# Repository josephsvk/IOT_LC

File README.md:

# IOT_LC

KiCad hardware project for the modular IoT controller.

## Project files

- `IOT_LC.kicad_pro` — KiCad project settings
- `IOT_LC.kicad_sch` — schematic
- `IOT_LC.kicad_pcb` — PCB layout
- `IOT_LC.kicad_dru` — custom design rules
- `IOT_LC.csv` — component list

**Status:** Work in progress; not validated for production.

**Safety:** The design includes mains voltage. It has not been certified or validated for safe mains operation. Do not assume it is safe to manufacture or energize.

## Automatic PCB render

The user systemd path watcher monitors `IOT_LC.kicad_pcb`. After the file has
been unchanged for 2.5 seconds, it regenerates the top and bottom 3D renders.
The watcher unit files are in `systemd/`; the manual command is
`./rychle-spustenie/render.sh`.

<!-- AUTO-DOCS-START -->
## Schematic documentation

### Complete active hierarchical schematic

**Page 1**

[View vector PDF](docs/pdf/schematic.pdf)

## PCB documentation

### PCB front

**Page 1**

[View vector PDF](docs/pdf/pcb-front.pdf)

### PCB back

**Page 1**

[View vector PDF](docs/pdf/pcb-back.pdf)

### 3D render — pohľad zhora

### 3D render — pohľad zdola

<!-- AUTO-DOCS-END -->

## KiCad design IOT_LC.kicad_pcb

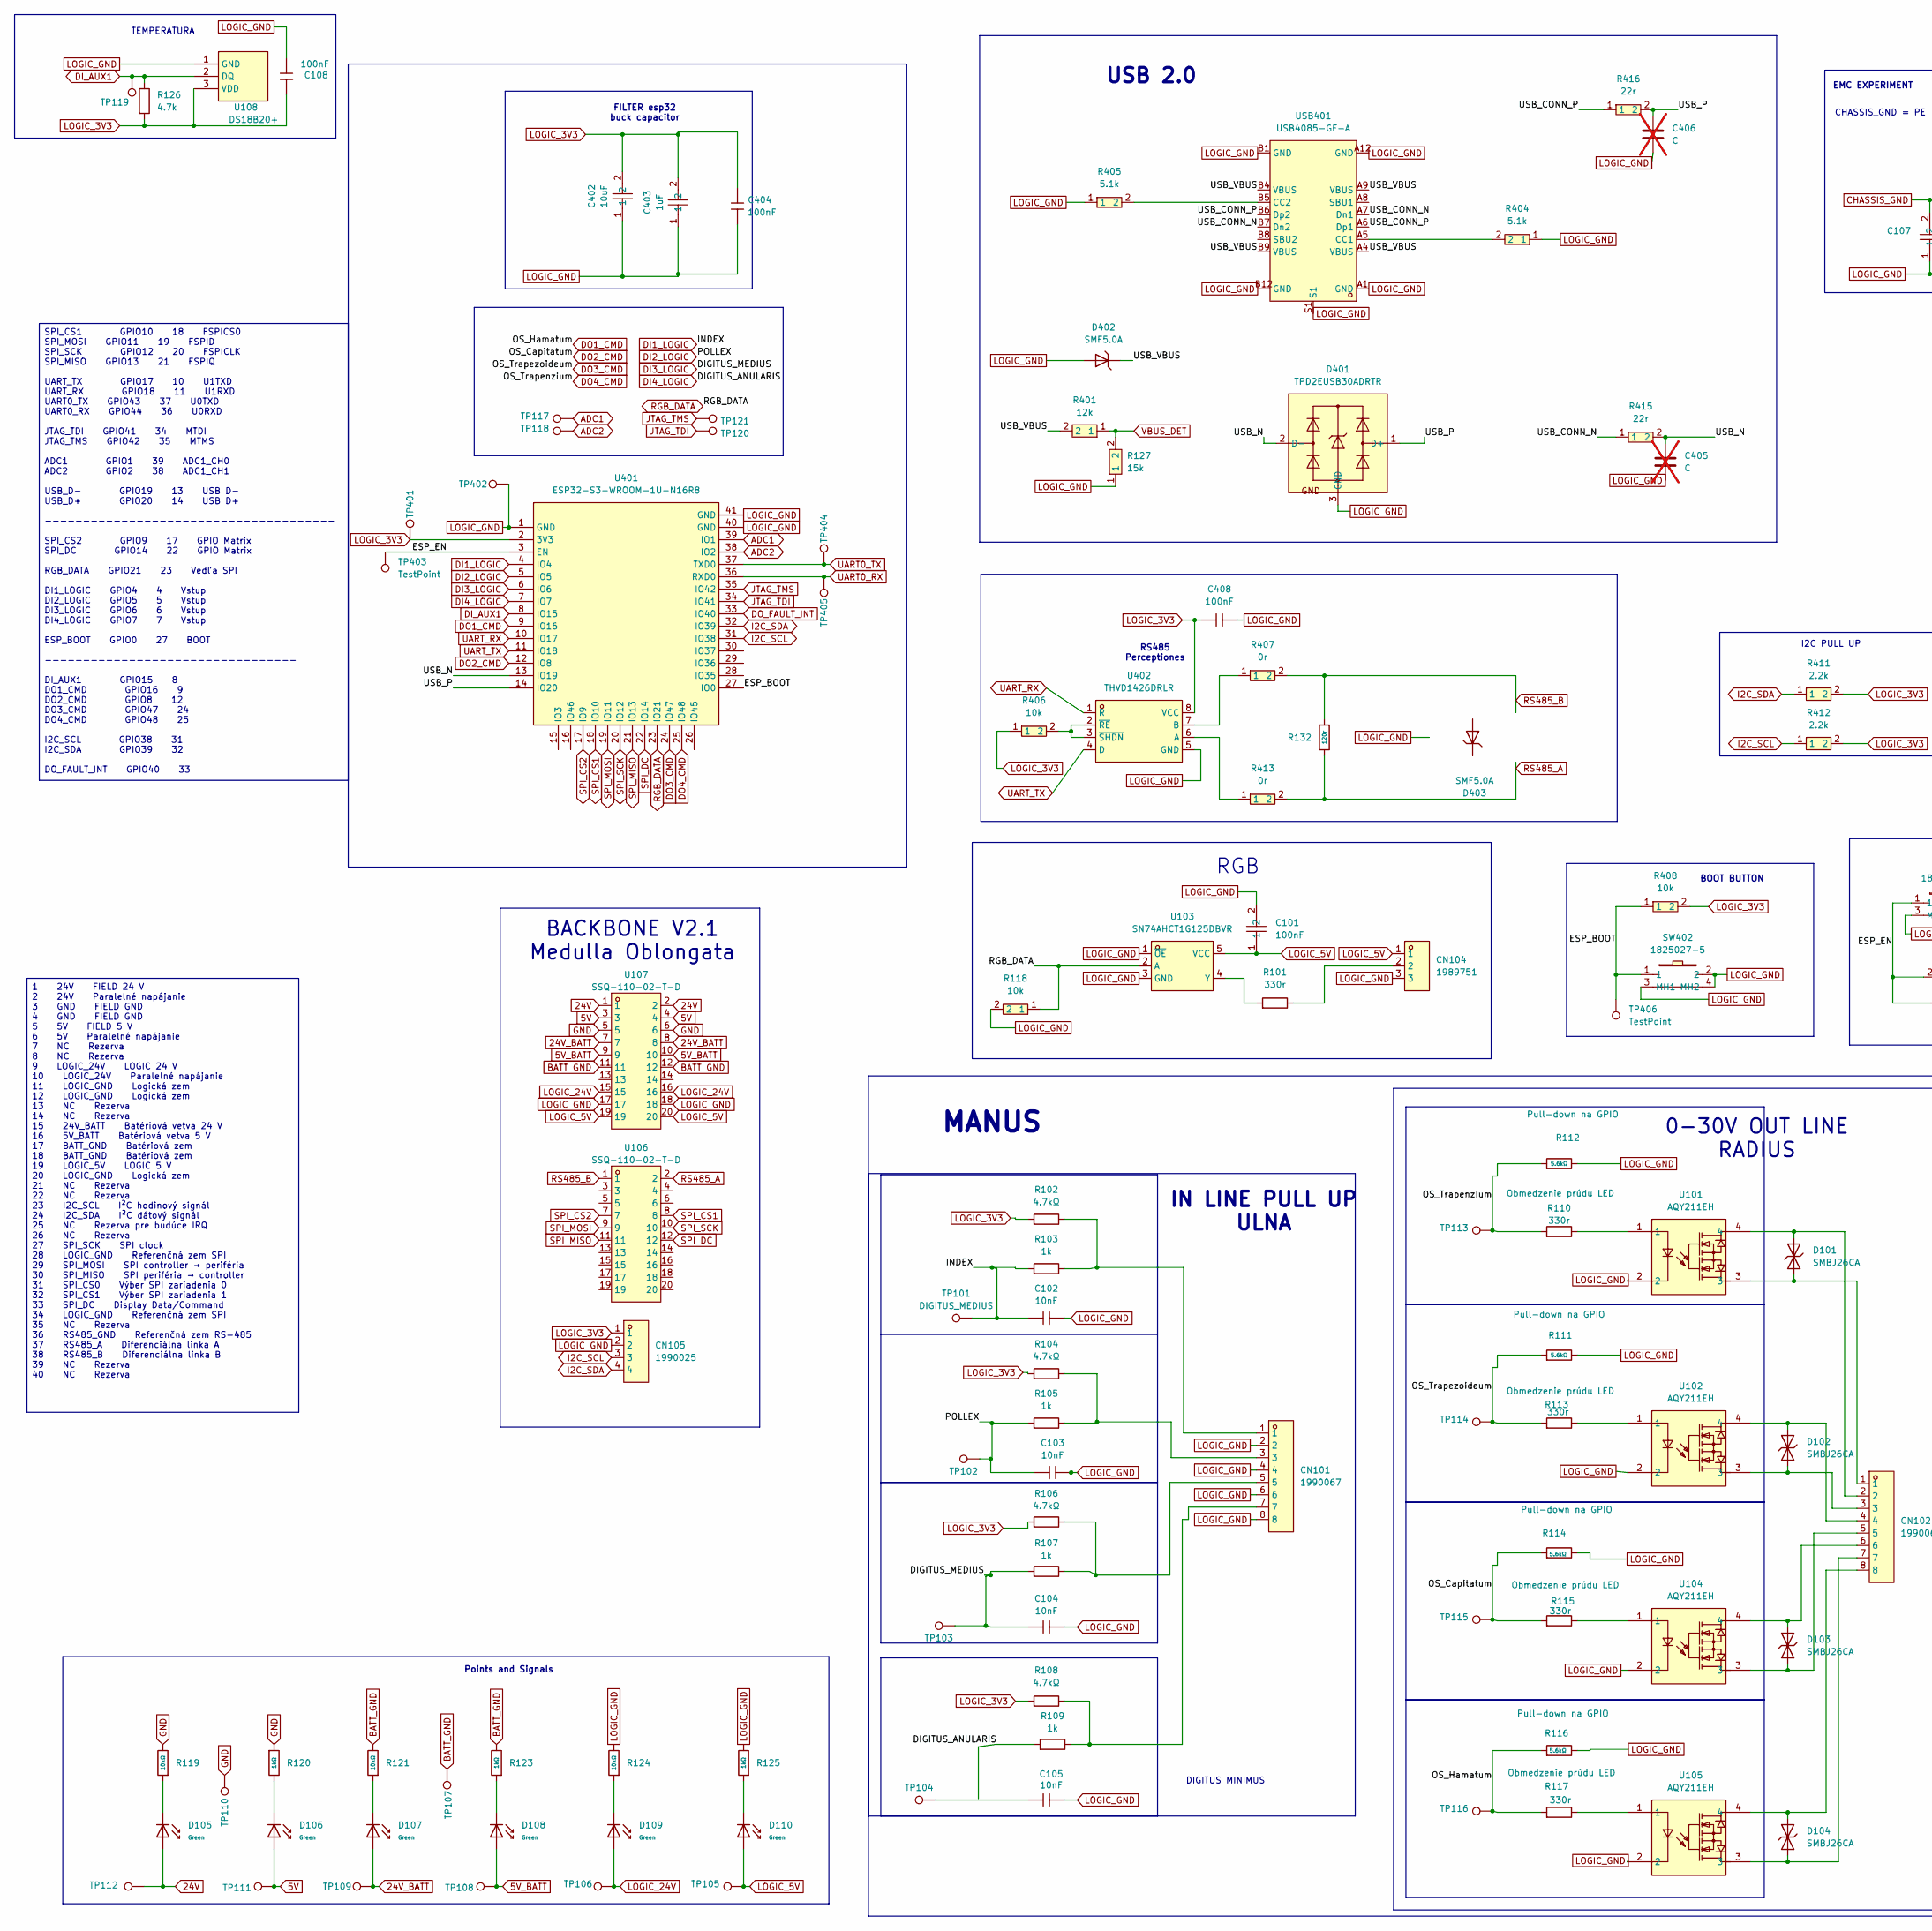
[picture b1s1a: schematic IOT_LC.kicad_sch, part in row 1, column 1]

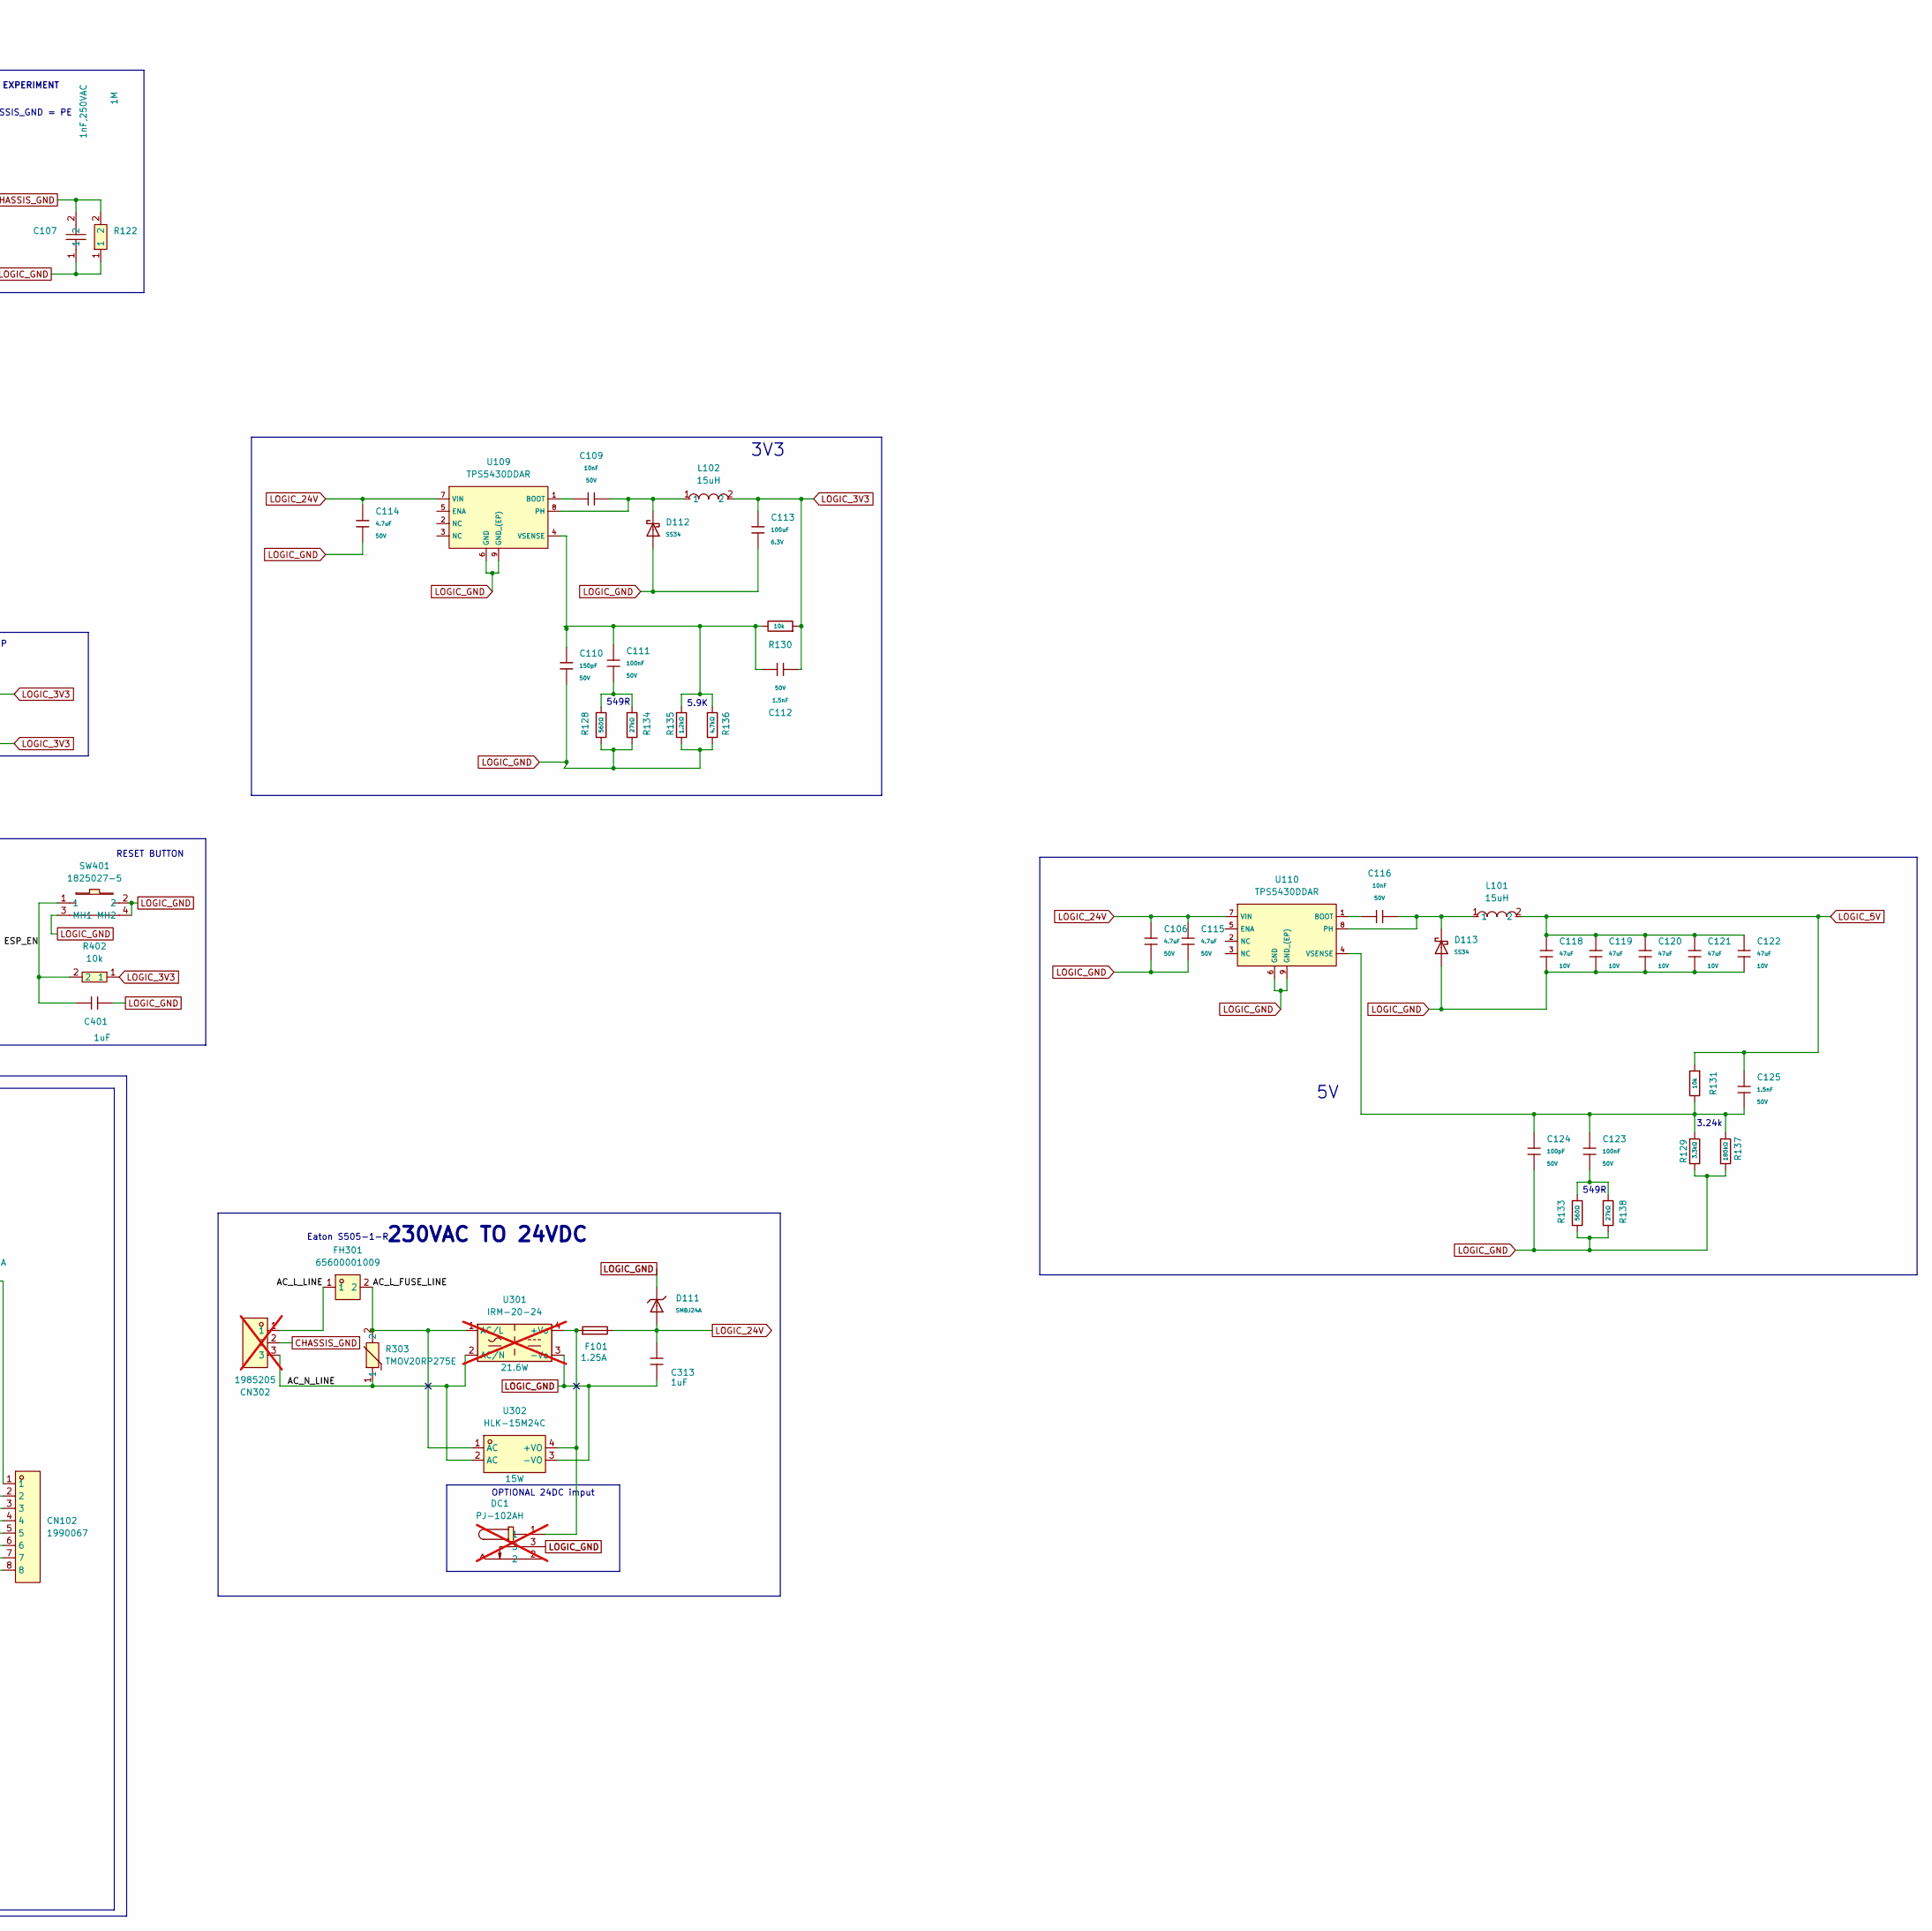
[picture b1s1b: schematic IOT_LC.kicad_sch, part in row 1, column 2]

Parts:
C101: 100nF; C_0603; MPN C0805C104K5RACTU; LCSC Part # C14663
C102, C103, C104, C105: 10nF; C_0603; MPN C0603C103K5RACTU; LCSC Part # C57112
C106, C114, C115: 4.7uF; C_1206; Voltage Rated 50V; Tolerance ±10%; Part 1206B475K500NT; LCSC C29823
C107: 1nF,250VAC; CAP-TH_L7.0-W4.0-P10.00-D0.6; MPN DE1E3RA102MA4BN01F; LCSC Part # C373381
C108, C404, C408: 100nF; C0603; MPN C0603C104K4RACTU; LCSC Part # C1525
C109, C116: 10nF; C_0603; Voltage Rated 50V; Tolerance ±10%; Part 0603B103K500NT; LCSC C57112
C110: 150pF; C_0603; Voltage Rated 50V; Tolerance ±10%; Part 0603B151K500NT; LCSC C1594
C111, C123: 100nF; C_0603; Voltage Rated 50V; Tolerance ±10%; Part CC0603KRX7R9BB104; LCSC C14663
C112: 1.5nF; C_0805; Voltage Rated 50V; Tolerance ±10%; Part 0805B152K500NT; LCSC C1717
C113: 100uF; C_1206; Voltage Rated 6.3V; Tolerance ±20%; Part CL31A107MQHNNNE; LCSC C15008
C118, C119, C120, C121, C122: 47uF; C_1206; Voltage Rated 10V; Tolerance ±20%; Part CL31A476MPHNNNE; LCSC C96123
C124: 100pF; C_0603; Voltage Rated 50V; Tolerance ±5%; Part CL10C101JB8NNNC; LCSC C14858
C125: 1.5nF; C_0603; Voltage Rated 50V; Tolerance ±10%; Part 0603B152K500NT; LCSC C1595
C313: 1uF; C0805; MPN CC0805JKX7R9BB105; LCSC Part # C28323
C401: 1uF; C0805; MPN C1206C105K5RACTU; LCSC Part # C28323
C402: 10uF; C0805; MPN C2012X7R1A106K125AC; LCSC Part # C15850
C403: 1uF; C0603; MPN FCC0603B105K160CT; LCSC Part # C52923
C405, C406: C; not fitted
CN101, CN102: 1990067; CONN-TH_8P-P2.50_1990067; MPN 1990067; LCSC Part # C17327671
CN104: 1989751; CONN-TH_3P-P2.50_1989751; MPN 1989751; LCSC Part # C17585029
CN105: 1990025; CONN-TH_4P-P2.50_1990025; MPN 1990025; LCSC Part # C3020058
CN302: 1985205; CONN-TH_3P-P3.50_PHOENIX-CONTACT_1985205; MPN 1985205; LCSC Part # C3817619; not fitted
D101, D102, D103, D104: SMBJ26CA; D_SMB; Clamping Voltage 42.1V; Voltage - Breakdown 31.9V; MPN SMBJ26CA; LCSC Part # C83332
D105, D106, D107, D108, D109, D110: Green; D_0805; Part KT-0805G; LCSC C2297
D111: SMBJ24A; D_SMB; Part SMBJ24A; LCSC C19077578
D112, D113: SS34; D_SMA; Forward Voltage (Vf@If) 550mV@3A; Reverse Voltage (Vr) 40V; Part SS34; LCSC C8678
D401: TPD2EUSB30ADRTR; SOT-9X3-3_L1.0-W0.8-P0.35-LS1.0-BR; MPN TPD2EUSB30ADRTR; LCSC Part # C94934
D402: SMF5.0A; D_SOD-123FL; MPN SMF5.0A; LCSC Part # C151296
D403: SMF5.0A; D_SOD-123FL; MPN SM712.TCT; LCSC Part # C12067
DC1: PJ-102AH; DC-IN-TH_PJ-102AH; MPN PJ-102AH; LCSC Part # C3096093; not fitted
F101: 1.25A; Fuse_0603_1608Metric; Interrupt Rating 50A; Rated Voltage 63V; LCSC Part # C206965
FH301: 65600001009; FUSE-TH_65600001009; MPN 65600001009; LCSC Part # C187510
L101, L102: 15uH; IND-SMD_L11.6-W10.1; MPN BCIHP1040SC-150M; LCSC Part C2921232
R101, R110, R113, R115, R117: 330r; R0603; MPN ERJ3EKF3300V; LCSC Part # C23138
R102, R104, R106, R108: 4.7kΩ; R_0603; Tolerance ±1%; Overload Voltage (Max) 75V; MPN ERJPA3F4701V; LCSC Part # C441924
R103, R105, R107, R109: 1k; R0603; MPN ERJ3EKF1001V; LCSC Part # C21190
R111, R112, R114, R116: 5.6kΩ; R_0603; Tolerance ±1%; Overload Voltage (Max) 75V; MPN ERJ2RKF4702X; LCSC Part # C25792
R118, R402, R406, R408: 10k; R_0603; MPN ERA3AEB103V; LCSC Part # C25804
R119, R121, R124: 10kΩ; R_0603; Overload Voltage (Max) 75V; Tolerance ±1%; MPN ERJ2RKF4702X; LCSC C25804
R120, R123, R125: 1kΩ; R_0603; Overload Voltage (Max) 75V; Tolerance ±1%; Part 0603WAF1001T5E; LCSC C21190
R122: 1M; R1206; MPN CRCW12061M00FKEA; LCSC Part # C17927
R126: 4.7k; R_0603; LCSC Part # C23164
R127: 15k; R0603; MPN ERA-3APB153V; LCSC Part # C22809
R128, R133: 560Ω; R_0603; Overload Voltage (Max) 75V; Tolerance ±1%; Part 0603WAF5600T5E; LCSC C23204
R129: 3.3kΩ; R_0603; Overload Voltage (Max) 75V; Tolerance ±1%; Part 0603WAF3301T5E; LCSC C22978
R130, R131: 10k; R_0603; Overload Voltage (Max) 75V; Tolerance ±1%; Part 0603WAF1002T5E; LCSC C25804
R132: 120r; R_0603; Overload Voltage (Max) 75V; Tolerance ±1%; Part 0603WAF1200T5E; LCSC C22787
R134, R138: 27kΩ; R_0603; Overload Voltage (Max) 75V; Tolerance ±1%; Part 0603WAF2702T5E; LCSC C22967
R135: 1.2kΩ; R_0603; Overload Voltage (Max) 75V; Tolerance ±1%; Part 0603WAF1201T5E; LCSC C22765
R136: 4.7kΩ; R_0603; Overload Voltage (Max) 75V; Tolerance ±1%; Part 0603WAF4701T5E; LCSC C23162
R137: 180kΩ; R_0805; Overload Voltage (Max) 150V; Tolerance ±1%; Part 0805W8F1803T5E; LCSC C17501
R303: TMOV20RP275E; RES-TH_L23.0-W9.5-P8.50-D0.9-S4.50; MPN TMOV20RP275E; LCSC Part # C187710
R401: 12k; R0603; MPN ERJ3EKF1202V; LCSC Part # C22790
R404, R405: 5.1k; R0603; LCSC Part # C23186
R407, R413: 0r; R0603; MPN ERJ3GEY0R00V; LCSC Part # C21189
R411, R412: 2.2k; R0805; MPN AC0805FR-7W2K2L; LCSC Part # C17520
R415, R416: 22r; R0603; MPN ERJ3EKF22R0V; LCSC Part # C23345
SW401, SW402: 1825027-5; KEY-TH_4P-L7.5-W6.8-P4.50-LS7.2; MPN 1825027-5; LCSC Part # C86476
TP101: DIGITUS_MEDIUS; TestPoint_THTPad_1.0x1.0mm_Drill0.5mm
TP102, TP103, TP104, TP105, TP106, TP107, TP108, TP109, TP110, TP111, TP112, TP113, TP114, TP115, TP116, TP117, TP118, TP119, TP120, TP121, TP401, TP402, TP404, TP405: TestPoint_THTPad_1.0x1.0mm_Drill0.5mm
TP403, TP406: TestPoint; TestPoint_Pad_D1.0mm
U101, U102, U104, U105: AQY211EH; DIP-4_L6.4-W4.8-P2.54-LS7.6-BL; MPN AQY211EH; LCSC Part # C719541
U103: SN74AHCT1G125DBVR; SOT-23-5_L3.0-W1.7-P0.95-LS2.8-BR; MPN SN74AHCT1G125DBVR; LCSC Part # C7484
U106, U107: SSQ-110-02-T-D; HDR-TH_ESQ-110-23-G-D; MPN SSQ-110-02-T-D; LCSC Part # C5908768
U108: DS18B20+; TO-92-3_L4.9-W3.7-P1.27-L; MPN DS18B20+; LCSC Part # C9753
U109, U110: TPS5430DDAR; ESOP-8_L4.9-W3.9-P1.27-LS6.0-TL-EP; Output Voltage 1.221V~32.04V; Input Voltage 5.5V~36V; Part TPS5430DDAR; LCSC C9864
U301: IRM-20-24; Converter_ACDC_MeanWell_IRM-20-xx_THT; not fitted
U302: HLK-15M24C; PWRM-TH_4P-L47.5-W28.5_HLK-15MXXC; MPN HLK-15M24C; LCSC Part # C18203066
U401: ESP32-S3-WROOM-1U-N16R8; WIRELM-SMD_ESP32-S3-WROOM-1U; MPN ESP32-S3-WROOM-1U-N16R8; LCSC Part # C3013946
U402: THVD1426DRLR; SOT-583-8_L2.1-W1.2-P0.50-LS1.6-BR; MPN THVD1426DRLR; LCSC Part # C5215922
USB401: USB4085-GF-A; USC-C-SMD_USB4085-GF-A; MPN USB4085-GF-A; LCSC Part # C7095263

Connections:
5V: D106.2, TP111.1 (1_1), U107.3, U107.4
5V_BATT: D108.2, TP108.1 (1_1), U107.9, U107.10
24V: D105.2, TP112.1 (1_1), U107.1, U107.2
24V_BATT: D107.2, TP109.1 (1_1), U107.7, U107.8
/AC_L_FUSE_LINE: FH301.2, R303.2, U301.1 (AC/L), U302.1 (AC)
/AC_L_LINE: CN302.1, FH301.1
/AC_N_LINE: CN302.3, R303.1, U301.2 (AC/N), U302.2 (AC)
/ESP_BOOT: R408.1, SW402.1, TP406.1 (1_1), U401.27 (IO0)
/ESP_EN: C401.1, R402.2, SW401.1, TP403.1 (1_1), U401.3 (EN)
/USB_CONN_N: R415.1, USB401.A7 (Dn1), USB401.B7 (Dn2)
/USB_CONN_P: R416.1, USB401.A6 (Dp1), USB401.B6 (Dp2)
/USB_N: C405.1, D401.2 (D-), R415.2, U401.13 (IO19)
/USB_P: C406.1, D401.1 (D+), R416.2, U401.14 (IO20)
/USB_VBUS: D402.1, R401.2, USB401.A4 (VBUS), USB401.A9 (VBUS), USB401.B4 (VBUS), USB401.B9 (VBUS)
ADC1: TP117.1 (1_1), U401.39 (IO1)
ADC2: TP118.1 (1_1), U401.38 (IO2)
BATT_GND: R121.2, R123.2, TP107.1 (1_1), U107.11, U107.12
CHASSIS_GND: C107.2, CN302.2, R122.2; also elsewhere on the board
DI1_LOGIC: C102.1, R103.1, TP101.1 (1_1), U401.4 (IO4)
DI2_LOGIC: C103.1, R105.1, TP102.1 (1_1), U401.5 (IO5)
DI3_LOGIC: C104.1, R107.1, TP103.1 (1_1), U401.6 (IO6)
DI4_LOGIC: R109.1, U401.7 (IO7)
DI_AUX1: R126.1, TP119.1 (1_1), U108.2 (DQ), U401.8 (IO15)
DO1_CMD: R116.1, R117.1, TP116.1 (1_1), U401.9 (IO16)
DO2_CMD: R114.1, R115.1, TP115.1 (1_1), U401.12 (IO8)
DO3_CMD: R111.1, R113.1, TP114.1 (1_1), U401.24 (IO47)
DO4_CMD: R110.1, R112.1, TP113.1 (1_1), U401.25 (IO48)
DO_FAULT_INT: U401.33 (IO40)
GND: R119.2, R120.1, TP110.1 (1_1), U107.5, U107.6
I2C_SCL: CN105.3, R412.1, U401.31 (IO38)
I2C_SDA: CN105.4, R411.1, U401.32 (IO39)
JTAG_TDI: TP120.1 (1_1), U401.34 (IO41)
JTAG_TMS: TP121.1 (1_1), U401.35 (IO42)
LOGIC_3V3: C108.2, C112.2, C113.1, C402.2, C403.2, C404.2, C408.1, CN105.1, L102.2, R102.1, R104.1, R106.1, R108.1, R126.2, R130.1, R402.1, R406.1, R408.2, R411.2, R412.2, TP401.1 (1_1), U108.3 (VDD), U401.2 (3V3), U402.8 (VCC)
LOGIC_5V: C101.1, C118.1, C119.1, C120.1, C121.1, C122.1, C125.1, CN104.1, D110.2, L101.2, R131.1, TP105.1 (1_1), U103.5 (VCC), U107.19, U107.20; also elsewhere on the board
LOGIC_24V: C106.1, C114.1, C115.1, C313.2, D109.2, D111.2, F101.1, TP106.1 (1_1), U107.15, U107.16, U109.7 (VIN), U110.7 (VIN)
LOGIC_GND: C101.2, C102.2, C103.2, C104.2, C105.2, C106.2, C107.1, C108.1, C110.2, C113.2, C114.2, C115.2, C118.2, C119.2, C120.2, C121.2, C122.2, C124.2, C313.1, C401.2, C402.1, C403.1, C404.1, C405.2, C406.2, C408.2, CN101.2, CN101.4, CN101.6, CN101.8, CN104.3, CN105.2, D111.1, D112.2, D113.2, D401.3 (GND), D402.2, DC1.3, R111.2, R112.2, R114.2, R116.2, R118.2, R122.1, R124.2, R125.2, R127.1, R128.2, R129.2, R133.2, R134.2, R135.2, R136.2, R137.2, R138.2, R404.1, R405.1, SW401.2, SW401.3 (MH1), SW401.4 (MH2), SW402.2, SW402.3 (MH1), SW402.4 (MH2), TP402.1 (1_1), U101.2, U102.2, U103.1 (~OE), U103.3 (GND), U104.2, U105.2, U107.17, U107.18, U108.1 (GND), U109.6 (GND), U109.9 (GND_(EP)), U110.6 (GND), U110.9 (GND_(EP)), U301.3 (-Vo), U302.3 (-VO), U401.1 (GND), U401.40 (GND), U401.41 (GND), U402.5 (GND), USB401.A1 (GND), USB401.A12 (GND), USB401.B1 (GND), USB401.B12 (GND), USB401.S1; also elsewhere on the board
unnamed: C105.1, TP104.1 (1_1)
unnamed: C111.2, R128.1, R134.1
unnamed: C123.2, R133.1, R138.1
unnamed: CN101.1, R102.2, R103.2
unnamed: CN101.3, R104.2, R105.2
unnamed: CN101.5, R106.2, R107.2
unnamed: CN101.7, R108.2, R109.2
unnamed: CN102.1, D101.1, U101.3
unnamed: CN102.2, D101.2, U101.4
unnamed: CN102.3, D102.1, U102.3
unnamed: CN102.4, D102.2, U102.4
unnamed: CN102.5, D103.1, U104.3
unnamed: CN102.6, D103.2, U104.4
unnamed: CN102.7, D104.1, U105.3
unnamed: CN102.8, D104.2, U105.4
unnamed: CN104.2, R101.2
unnamed: D105.1, R119.1
unnamed: D106.1, R120.2
unnamed: D107.1, R121.1
unnamed: D108.1, R123.1
unnamed: D109.1, R124.1
unnamed: D110.1, R125.1
unnamed: R110.2, U101.1
unnamed: R113.2, U102.1
unnamed: R115.2, U104.1
unnamed: R117.2, U105.1
unnamed: R101.1, U103.4 (Y)
unnamed: C109.1, U109.1 (BOOT)
unnamed: C109.2, D112.1, L102.1, U109.8 (PH)
unnamed: C110.1, C111.1, C112.1, R130.2, R135.1, R136.1, U109.4 (VSENSE)
unnamed: C116.1, U110.1 (BOOT)
unnamed: C116.2, D113.1, L101.1, U110.8 (PH)
unnamed: C123.1, C124.1, C125.2, R129.1, R131.2, R137.1, U110.4 (VSENSE)
unnamed: DC1.1, F101.2, U301.4 (+Vo), U302.4 (+VO)
unnamed: R413.1, U402.6 (A)
unnamed: R407.1, U402.7 (B)
unnamed: R406.2, U402.2 (~RE), U402.3 (~SHDN)
unnamed: R404.2, USB401.A5 (CC1)
unnamed: R405.2, USB401.B5 (CC2)
RGB_DATA: R118.1, U103.2 (A), U401.23 (IO21)
RS485_A: R132.2, R413.2, U106.2
RS485_B: R132.1, R407.2, U106.1
SPI_CS1: U106.8, U401.18 (IO10)
SPI_CS2: U106.7, U401.17 (IO9)
SPI_DC: U106.12, U401.22 (IO14)
SPI_MISO: U106.11, U401.21 (IO13)
SPI_MOSI: U106.9, U401.19 (IO11)
SPI_SCK: U106.10, U401.20 (IO12)
UART0_RX: TP405.1 (1_1), U401.36 (RXD0)
UART0_TX: TP404.1 (1_1), U401.37 (TXD0)
UART_RX: U401.10 (IO17), U402.1 (R)
UART_TX: U401.11 (IO18), U402.4 (D)
VBUS_DET: R127.2, R401.1

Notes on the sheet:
IN LINE PULL UP ULNA
BACKBONE V2.1 Medulla Oblongata
DIGITUS MINIMUS
Points and Signals
TEMPERATURA
RGB
0-30V OUT LINE RADIUS
BOOT BUTTON
3.24k
OPTIONAL 24DC imput
EMC EXPERIMENT
230VAC TO 24VDC
5.9K
I2C PULL UP
USB 2.0
MANUS
Eaton S505-1-R
549R
RS485 Perceptiones
3V3
RESET BUTTON
FILTER esp32 buck capacitor
CHASSIS_GND = PE
SPI_CS1 GPIO10 18 FSPICS0 SPI_MOSI GPIO11 19 FSPID SPI_SCK GPIO12 20 FSPICLK SPI_MISO GPIO13 21 FSPIQ UART_TX GPIO17 10 U1TXD UART_RX GPIO18 11 U1RXD UART0_TX GPIO43 37 U0TXD UART0_RX GPIO44 36 U0RXD JTAG_TDI GPIO41 34 MTDI JTAG_TMS GPIO42 35 MTMS ADC1 GPIO1 39 ADC1_CH0 ADC2 GPIO2 38 ADC1_CH1 USB_D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
1 24V FIELD 24 V 2 24V Paralelné napájanie 3 GND FIELD GND 4 GND FIELD GND 5 5V FIELD 5 V 6 5V Paralelné napájanie 7 NC Rezerva 8 NC Rezerva 9 LOGIC_24V LOGIC 24 V 10 LOGIC_24V Paralelné napájanie 11 LOGIC_GND Logická zem 12 LOGIC_GND Logická zem 13 NC Rezerva 14 NC Rezerva 15 24V_BATT Batériová ve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

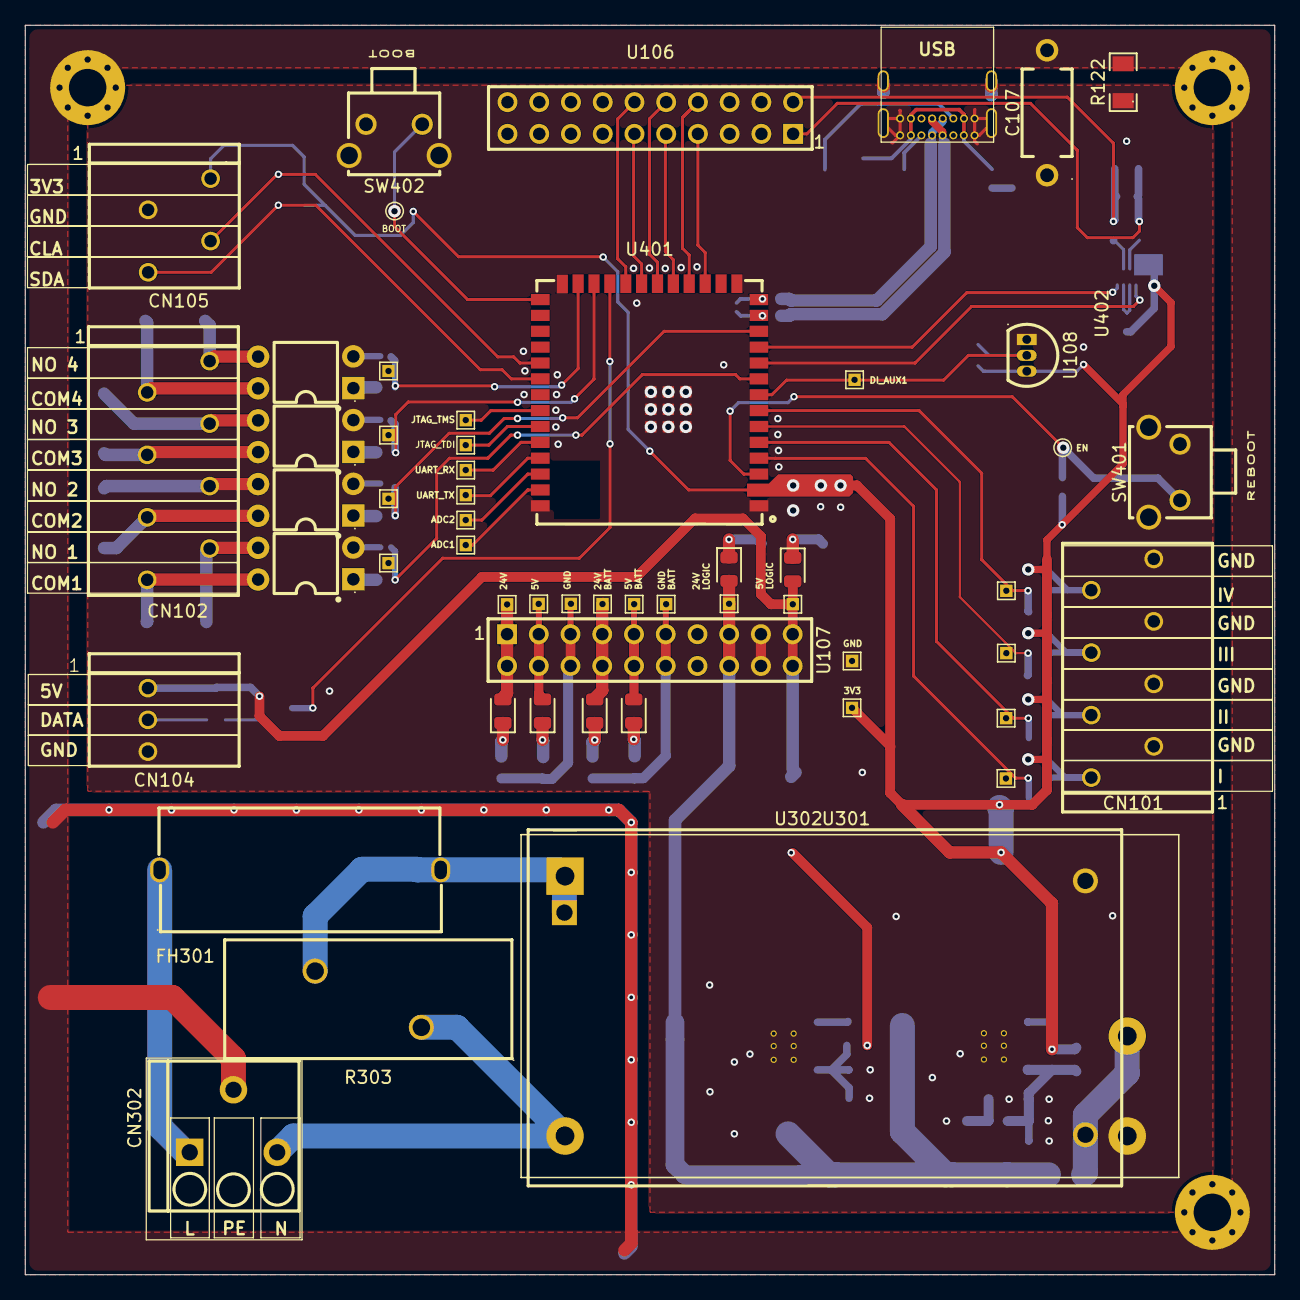
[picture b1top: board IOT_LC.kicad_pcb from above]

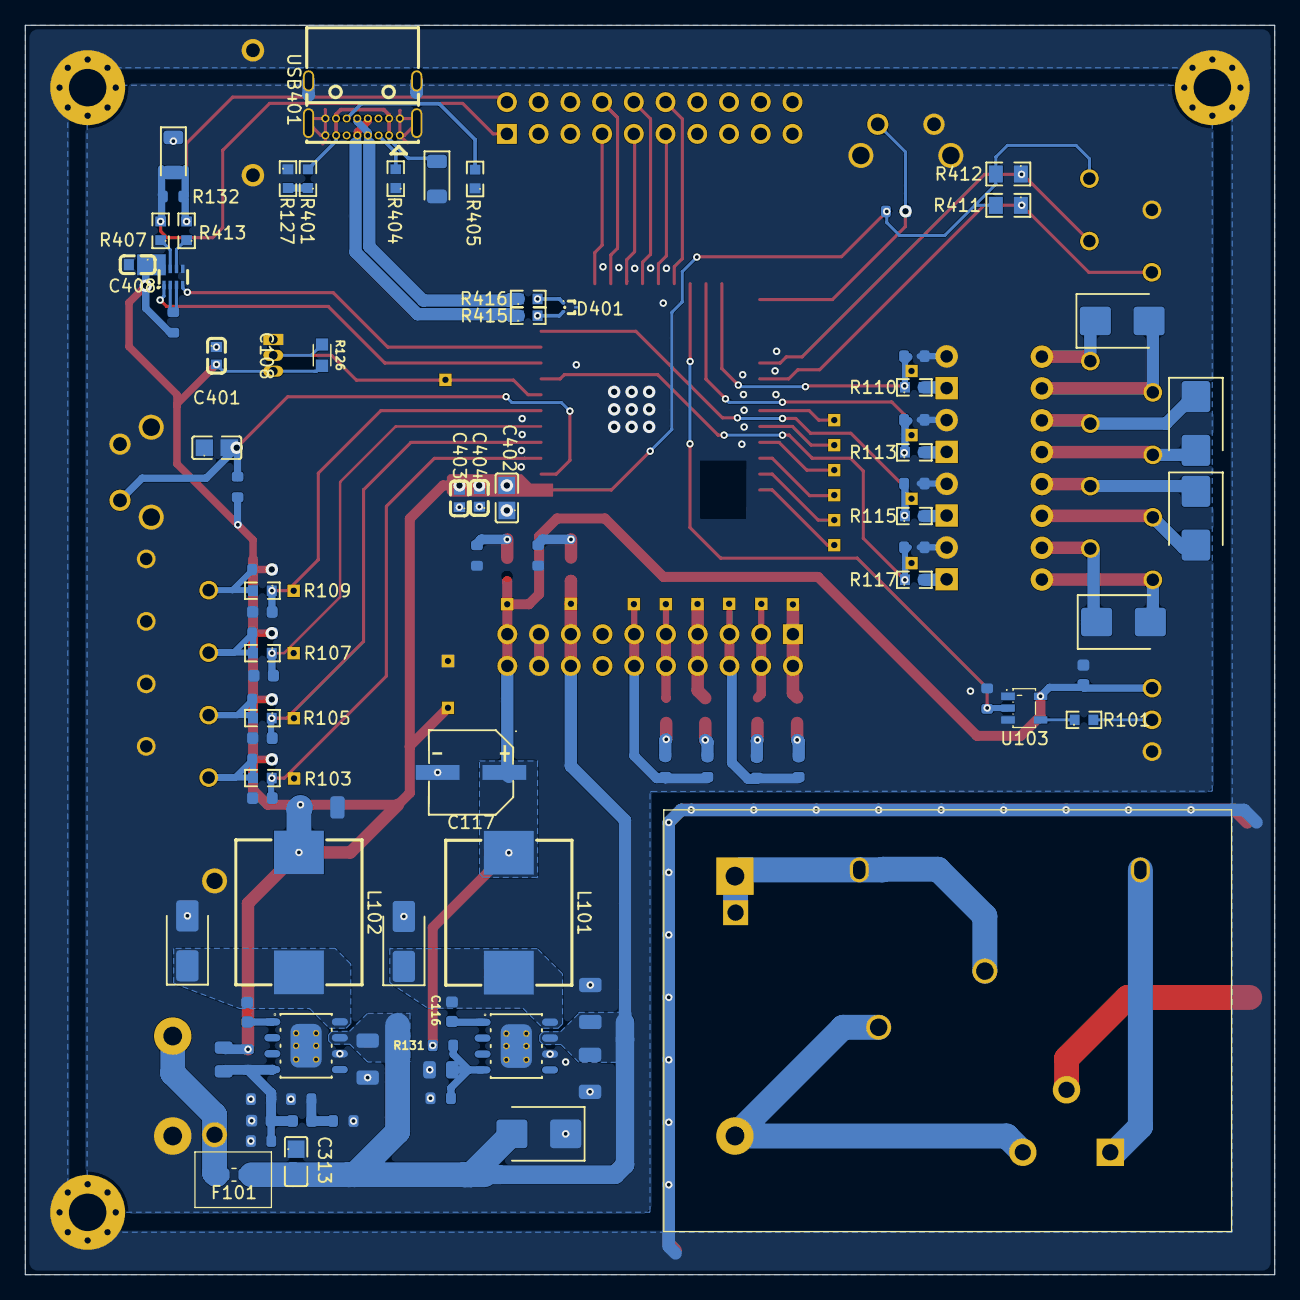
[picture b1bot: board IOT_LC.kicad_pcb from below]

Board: 2 copper layers, 100.0 x 100.0 mm, 144 parts (87 on the bottom side), 88 nets.

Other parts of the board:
C117: 220UF; CAP-SMD_BD6.3-L6.6-W6.6-LS7.2-FD
H301, H303, H304: MountingHole_Pad; MountingHole_3mm_Pad_Via

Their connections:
CHASSIS_GND: H301.1 (1_1), H303.1 (1_1), H304.1 (1_1); also elsewhere on the board
LOGIC_5V: C117.1; also elsewhere on the board
LOGIC_GND: C117.2; also elsewhere on the board

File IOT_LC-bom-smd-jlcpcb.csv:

Comment,Description,Designator,Footprint,LCSC Part #
100nF,,C101,0805,C3018562
10nF,,"C102,C103,C104,C105",0603,C116378
4.7uF,,C106,1210,
220UF,,C117,1210,
22uF,,"C118,C119",1210,
100nF,,"C108,C404,C408",0603,C2181816
10nF,,C109,1206,
150pF,,C110,1206,
100nF,,C111,1206,
1.5nF,,C112,1206,
100uF,,C113,0603,
4.7uF,,"C114,C115",0603,
10nF,,C116,0603,
1uF,,C313,0805,C541528
1uF,,C401,1206,C2167287
10uF,,C402,0805,C2167452
1uF,,C403,0603,C7419418
4.7nF,,C407,0603,C106218
SMBJ26CA,,"D101,D102,D103,D104",SMB_L4.6-W3.6-LS5.3-BI,C83332
SMBJ24A,,D111,SMB_L4.3-W3.6-LS5.4-RD,C224017
TPD2EUSB30ADRTR,,D401,SOT-9X3-3_L1.0-W0.8-P0.35-LS1.0-BR,C94934
SMF5.0A,,D402,SOD-123F_L2.8-W1.8-LS3.7-RD,C151296
SM712.TCT,,D403,SOT-23-3_L3.0-W1.7-P0.95-LS2.9-BR,C12067
1.25A,,F101,1206,
15uH,,L101,IND-SMD_L5.5-W5.3_APS0550M,C54123766
15uH,,L102,IND-SMD_L7.0-W6.6_CMKD-0630A,C41384282
330,,"R101,R110,R113,R115,R117",0603,C278617
1k,,"R103,R105,R107,R109",0603,C118155
4k7,,"R102,R104,R106,R108",0603,C441924
47k,,"R111,R112,R114,R116",0402,C413103
10k,,"R118,R402,R406,R408",0603,C190610
47k,,"R119,R121,R124",0805,
5k6,,"R120,R123,R125",0805,
1M,,R122,1206,C844869
4k7,,R126,0603,
15k,,R127,0603,C2089596
549_0603_0.1%,,R128,0603,
10k,,"R130,R131",0603,
5.9k_0603,,R129,0603,
12k,,R401,0603,C400645
5k1,,"R404,R405",0603,C543366
0,,"R407,R413",0603,C122704
60.4,,"R409,R410",0603,C844801
2k2,,"R411,R412",0805,C5545398
22,,"R415,R416",0603,C122707
SN74AHCT1G125DBVR,,U103,SOT-23-5_L3.0-W1.7-P0.95-LS2.8-BR,C7484
TPS5430DDAR,,"U109,U110",SOT-23-6_L2.9-W1.6-P0.95-LS2.8-BL,C5185863
ESP32-S3-WROOM-1U-N16R8,,U401,WIRELM-SMD_ESP32-S3-WROOM-1U,C3013946
THVD1426DRLR,,U402,SOT-583-8_L2.1-W1.2-P0.50-LS1.6-BR,C5215922
USB4085-GF-A,,USB401,USC-C-SMD_USB4085-GF-A,C7095263
